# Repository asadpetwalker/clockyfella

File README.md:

# clockyfella

# Why i made this project

I get late to school everyday because I sleep in late so I made an alarm clock to wake me up.

# Images

# BOM
| Qty | Part            | Manufacturer Part # | Description                          | DigiKey Part #                | Unit Price | Total  |
| --- | --------------- | ------------------- | ------------------------------------ | ----------------------------- | ---------- | ------ |
| 2   | Piezo Buzzer    | PS1240P02BT         | 3V piezo buzzer, 12.2mm TH           | 445-2525-1-ND                 | $0.57      | $1.14  |
| 10  | 10µF Capacitor  | CL21A106KPFNNNG     | 10µF 10V X5R 0805 ceramic capacitor  | 1276-6456-1-ND                | $0.058     | $0.58  |
| 10  | 1µF Capacitor   | CL21B105KAFNNNE     | 1µF 25V X7R 0805 ceramic capacitor   | 1276-1066-1-ND                | $0.049     | $0.49  |
| 10  | 0.1µF Capacitor | CL21B104KBCNNNC     | 0.1µF 50V X7R 0805 ceramic capacitor | 1276-1003-1-ND                | $0.038     | $0.38  |
| 10  | 10kΩ Resistor   | RC0603FR-0710KL     | 1% 1/10W 0603 resistor               | 311-10.0KHRCT-ND              | $0.024     | $0.24  |
| 10  | 5.1kΩ Resistor  | RC0603FR-075K1L     | 1% 1/10W 0603 resistor               | 311-5.10KHRCT-ND              | $0.024     | $0.24  |
| 1   | RTC IC          | DS3231M+TRL         | I2C RTC clock/calendar IC (SOIC-16)  | DS3231M+TRLCT-ND              | $13.09     | $13.09 |
| 10  | 3.3V Regulator  | NCP1117LPST33T3G    | 3.3V 1A linear regulator (SOT-223)   | NCP1117LPST33T3GOSCT-ND       | $0.262     | $2.62  |
| 2   | ESP32-S3 Module | ESP32-S3-WROOM-1-N4 | WiFi + Bluetooth module              | 1965-ESP32-S3-WROOM-1-N4CT-ND | $5.21      | $10.42 |
| 4   | TVS Diode       | TVS1400DRVR         | Precision surge protection diode     | 296-50511-1-ND                | $1.03      | $4.12  |

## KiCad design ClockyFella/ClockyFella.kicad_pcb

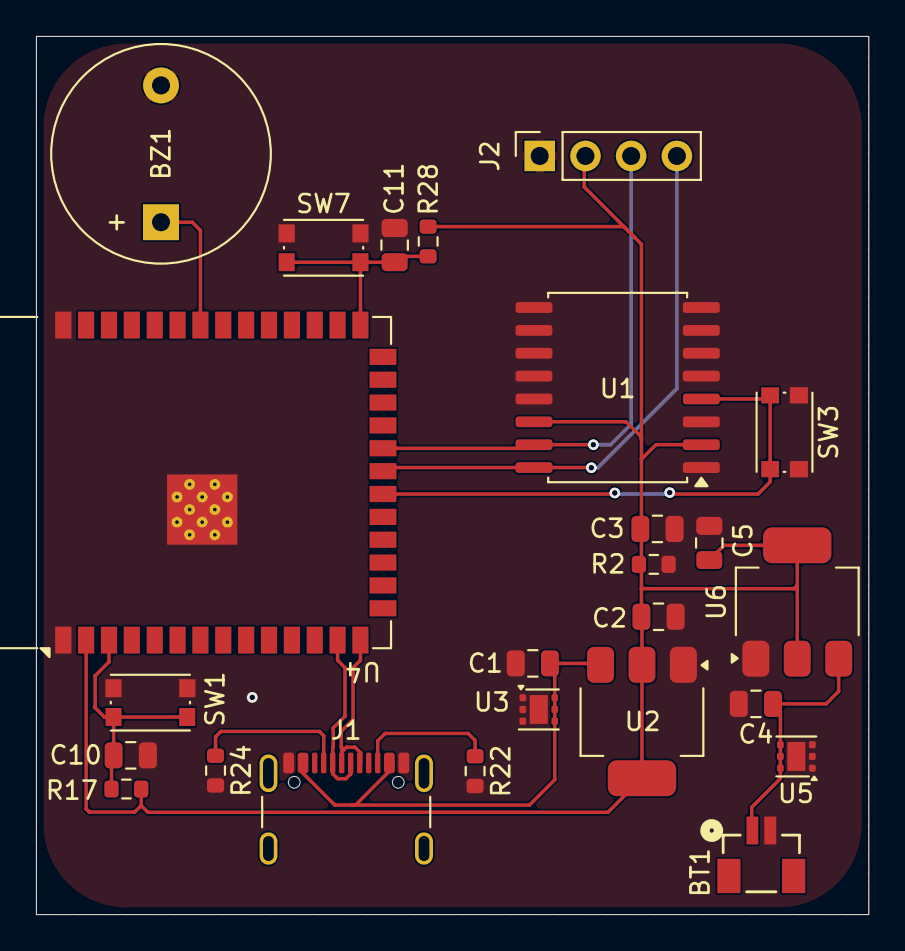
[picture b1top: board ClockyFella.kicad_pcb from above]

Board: 2 copper layers, 46.2 x 48.8 mm, 25 parts (0 on the bottom side), 14 nets.

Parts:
BT1: Battery; CONN_BM02B-SRSS-TB_JST
BZ1: Buzzer; Buzzer_12x9.5RM7.6
C1, C2, C4, C5: 10u; C_0805_2012Metric
C3: 1u; C_0805_2012Metric
C10, C11: 100n; C_0805_2012Metric
J1: USB_C_Receptacle_USB2.0_14P; USB_C_Receptacle_GCT_USB4105-xx-A_16P_TopMnt_Horizontal
J2: PinSocket_1x04_P2.54mm_Vertical
R2, R17, R28: 10k; R_0603_1608Metric
R22, R24: 5.1k; R_0603_1608Metric
SW1: RST; SW_Push_1P1T_NO_CK_KMR2
SW3: SW_Push; SW_Push_1P1T_NO_CK_KMR2
SW7: BOOT; SW_Push_1P1T_NO_CK_KMR2
U1: DS3231M; SOIC-16W_7.5x10.3mm_P1.27mm
U2, U6: NCP1117-3.3_SOT223; SOT-223-3_TabPin2
U3, U5: TVS1400DRV; WSON-6-1EP_2x2mm_P0.65mm_EP1x1.6mm
U4: ESP32-S3-WROOM-1

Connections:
+3V3: C2.1, C3.1, C5.1, J2.2, R2.1, R17.1, R28.1, U1.2 (VCC), U1.14 (VBAT), U2.2 (VO), U4.2 (3V3), U6.2 (VO)
+5V: C1.1, J1.A4 (VBUS), J1.A9 (VBUS), J1.B4 (VBUS), J1.B9 (VBUS), U2.3 (VI), U3.4 (IN), U3.5 (IN), U3.6 (IN)
/D+: J1.A6 (D+), J1.B6 (D+), U4.14 (USB_D+)
/D-: J1.A7 (D-), J1.B7 (D-), U4.13 (USB_D-)
/SCL: J2.4, U1.16 (SCL), U4.21 (IO13)
/SDA: J2.3, U1.15 (SDA), U4.22 (IO14)
/~RST: SW3.2, U1.4 (~RST), U4.20 (IO12)
GND: BT1.2 (-), BZ1.2 (-), C1.2, C2.2, C3.2, C4.2, C5.2, C10.2, C11.2, J1.A1 (GND), J1.A12 (GND), J1.B1 (GND), J1.B12 (GND), J2.1, R2.2, R22.2, R24.2, SW1.1, SW3.1, SW7.1, U1.1 (32KHZ), U1.3 (~INT/SQW), U1.5 (GND), U1.6 (GND), U1.7 (GND), U1.8 (GND), U1.9 (GND), U1.10 (GND), U1.11 (GND), U1.12 (GND), U1.13 (GND), U2.1 (GND), U3.1 (GND), U3.2 (GND), U3.3 (GND), U3.7 (GND), U4.1 (GND), U4.40 (GND), U4.41 (GND), U5.1 (GND), U5.2 (GND), U5.3 (GND), U5.7 (GND), U6.1 (GND)
unnamed: BT1.1 (+), C4.1, U5.4 (IN), U5.5 (IN), U5.6 (IN), U6.3 (VI)
unnamed: BZ1.1 (+), U4.34 (IO41)
unnamed: J1.A5 (CC1), R24.1
unnamed: J1.B5 (CC2), R22.1
unnamed: C10.1, R17.2, SW1.2, U4.3 (EN)
unnamed: C11.1, R28.2, SW7.2, U4.27 (IO0)

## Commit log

2026-05-13 the stuff
2026-05-13 code
2026-05-24 enclosures
